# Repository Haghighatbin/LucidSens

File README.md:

# LucidSens

<b>A device for electrochemiluminescence (ECL)-based measurements</b><br /><br />

<p align='justify'>
  There is a common agreement that the most indicative clinical procedure for rapid and early diagnosis of diseases is to monitor the concentration of specific biomarkers in the patient’s analytical sample at the early stages of the incident using point-of-care (POC) technologies. Among the POC sensing devices, luminescence-based sensing methodologies have been a dominant trend in clinical procedures mostly owing to their tremendously high sensitivity, specificity and rapidity in the analysis of multiplex analytical samples. However, achieving high photosensitivity and versatility to process multiple samples in luminescence-based POC devices commonly come at a cost of compromising the affordability aspect of such sensing devices. <br /><br />To address the gap, <b>LucidSens</b>, a cost-effective luminescence-based POC sensing device is developed for highly sensitive and precise determination of electrochemiluminescence (ECL) and chemiluminescence (CL)-based biological samples. While designed to be portable and cost-efficient, the device provides the versatility of operating in two operational modes: <b>incubation</b> and <b>detection</b> modes. In the incubation mode, the integrity of the process is validated and assured by a PID (proportional, integral, derivative) algorithm with a temperature-sensing feedback loop controlling the implemented Peltier heating/cooling module. In the detection mode, the system is capable of collecting ECL/CL signals of up to 18 analytical samples utilizing an implemented silicon-photomultiplier (SiPM) biased by a miniaturized onboard high-voltage power supply and built-in pseudo-potentiostat modules. The portable architecture of the device as well as remarkable photosensitivity, cost-efficiency and convenient operational instruction may propose the current platform as a versatile analytical template to be adapted for a wide range of ECL/CL-based clinical and bio-analytical determinations.</p><br />
  
Designed and developed by <b><aminhb@tutanota.com></b>

# Firmware
The firmware has been written in Micropython (Loboris port ESP32_LoBo_v3.2.24) based on Espressif ESP32-WROVER-B/I modules with 4MB external SPI flash and 8MB PSRAM.<br />
https://github.com/Haghighatbin/LucidSens/tree/master/Firmware

# Software
Created by: PyQt5 and UI code generator 5.15.4 - sourcefile was written in Python 3.5<br />
https://github.com/Haghighatbin/LucidSens/tree/master/Software   <br />
[Screenshot]

# PCB Layout and Schematics
https://github.com/Haghighatbin/LucidSens/tree/master/PCB_Schematics_Layouts

# CAD files
https://github.com/Haghighatbin/LucidSens/tree/master/CADs

# 3D View
https://user-images.githubusercontent.com/10771949/146338794-2b45d992-ebb1-41cf-bab1-338458c2112e.mp4

# Blueprint

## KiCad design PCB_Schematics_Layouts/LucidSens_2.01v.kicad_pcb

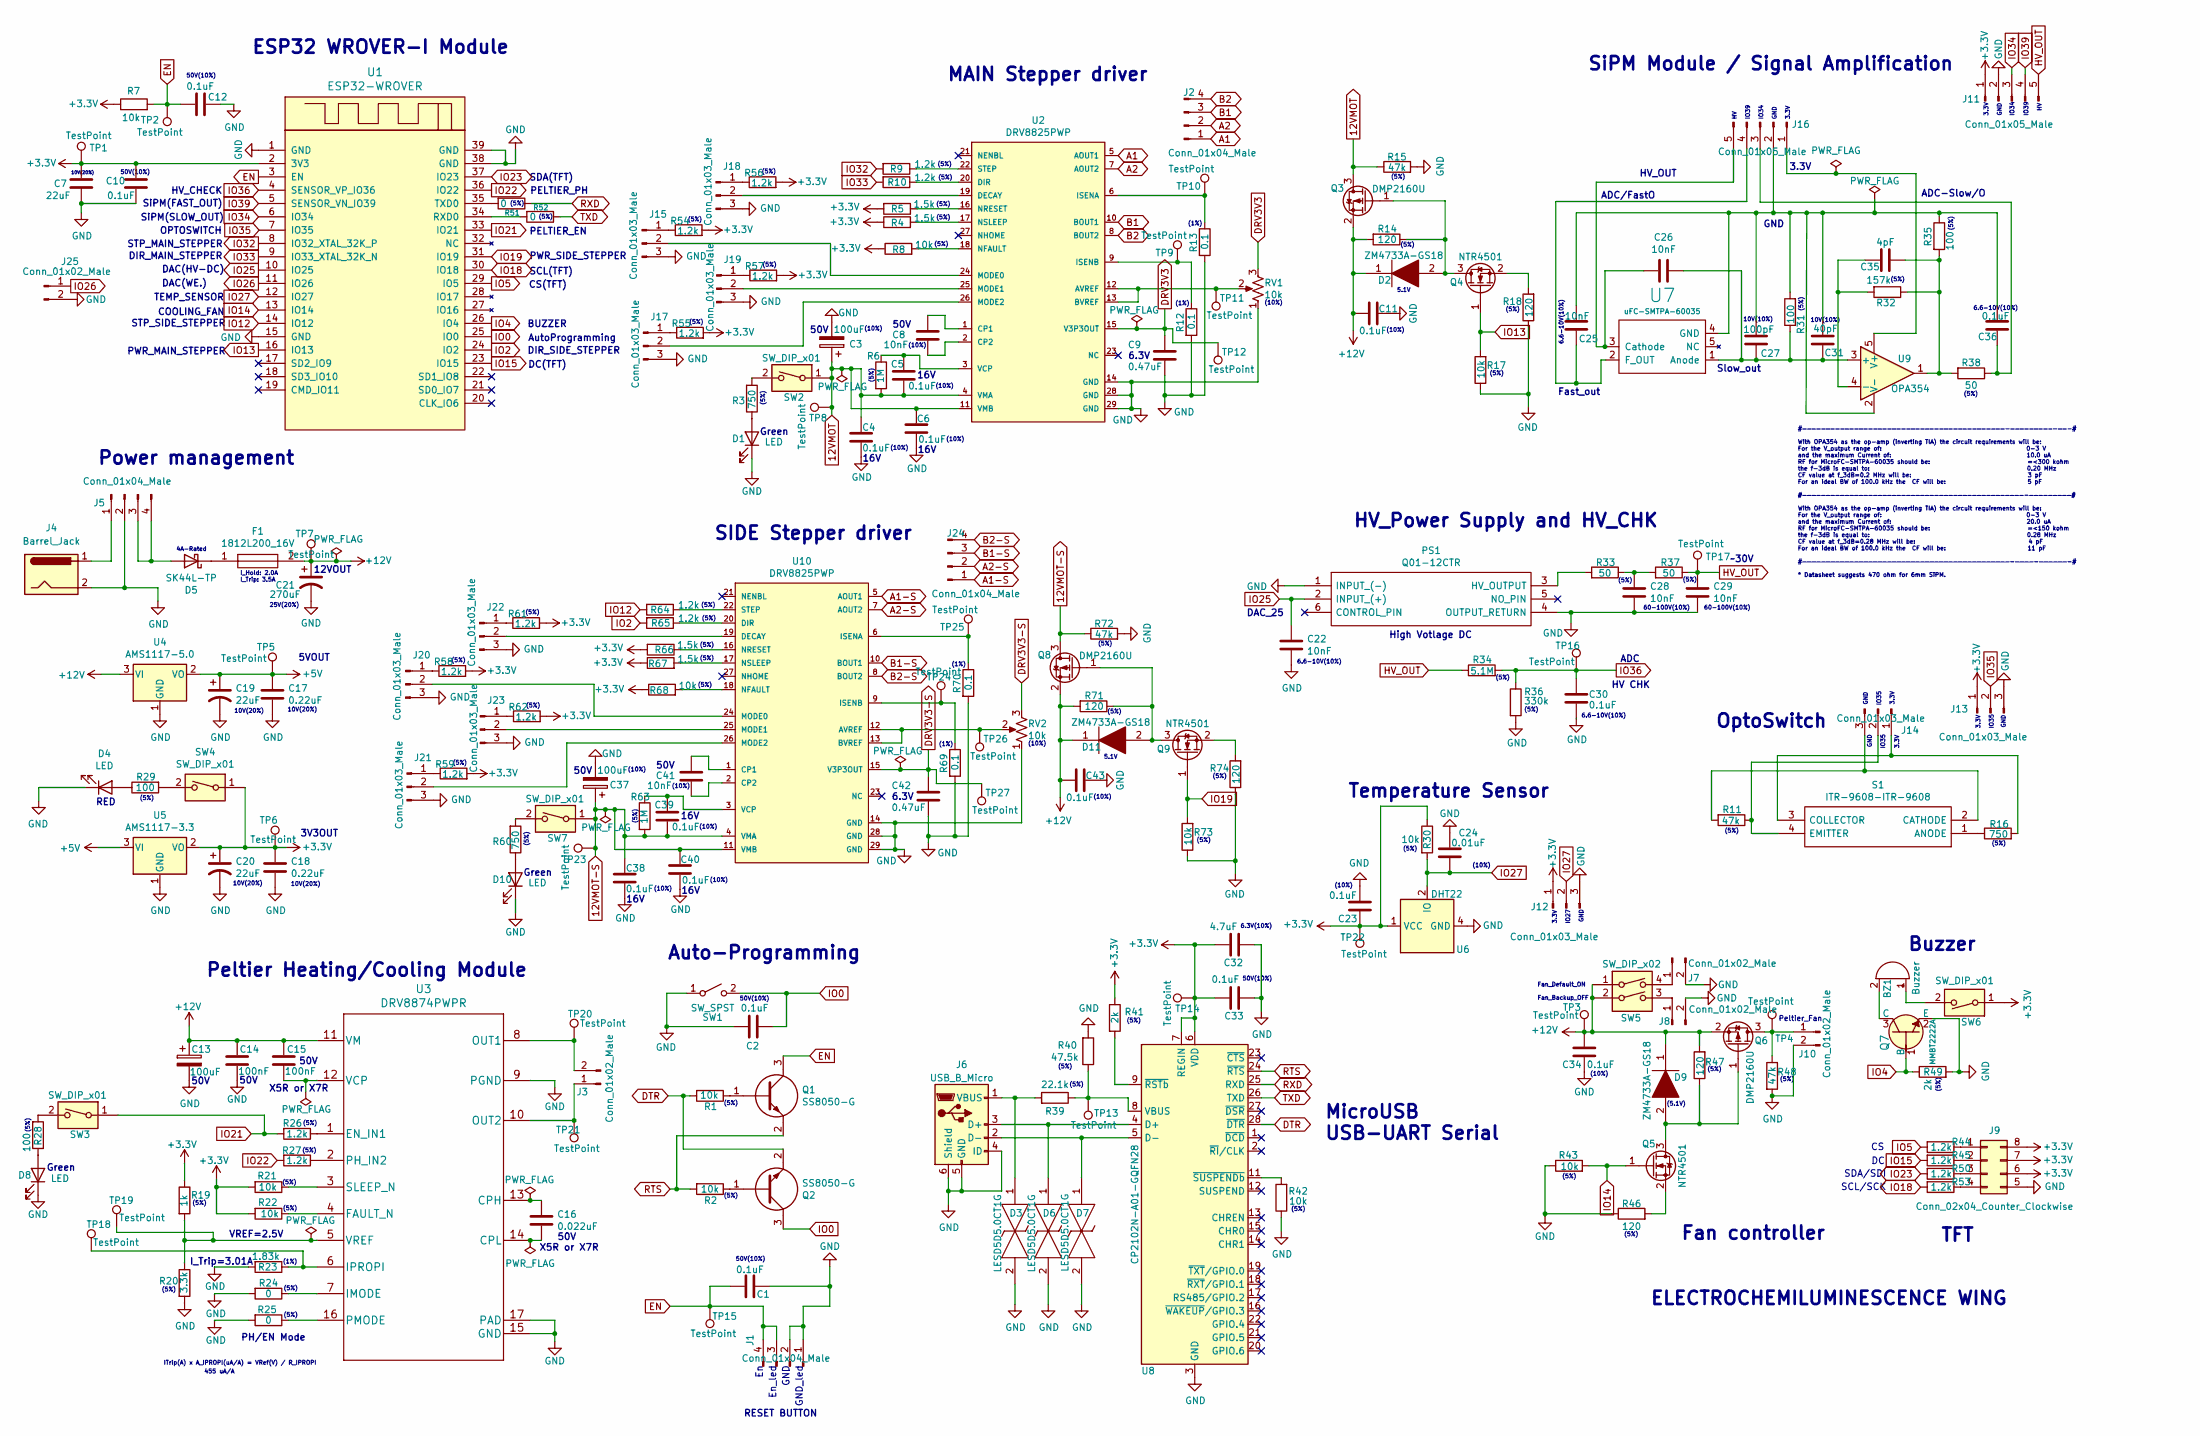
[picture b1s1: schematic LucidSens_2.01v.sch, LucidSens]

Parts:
BZ1: Buzzer; Buzzer_12x9.5RM7.6
C1, C2, C4, C5, C6, C10, C11, C12, C23, C30, C33, C34, C36, C38, C39, C40, C43: 0.1uF; C_0805_2012Metric_Pad1.18x1.45mm_HandSolder
C3, C13, C37: 100uF; CAPAE660X800N
C7: 22uF; C_0805_2012Metric_Pad1.18x1.45mm_HandSolder
C8, C22, C25, C26, C28, C29, C41: 10nF; C_0805_2012Metric_Pad1.18x1.45mm_HandSolder
C9, C42: 0.47uF; C_0805_2012Metric_Pad1.18x1.45mm_HandSolder
C14, C15: 100nF; C_0805_2012Metric_Pad1.18x1.45mm_HandSolder
C16: 0.022uF; C_0805_2012Metric_Pad1.18x1.45mm_HandSolder
C17, C18: 0.22uF; C_0805_2012Metric_Pad1.18x1.45mm_HandSolder
C19, C20: 22uF; CAPAE530X610N
C21: 270uF; CAPAE830X1050N
C24: 0.01uF; C_0805_2012Metric_Pad1.18x1.45mm_HandSolder
C27: 100pF; C_0805_2012Metric_Pad1.18x1.45mm_HandSolder
C31: 40pF; C_0805_2012Metric_Pad1.18x1.45mm_HandSolder
C32: 4.7uF; C_0805_2012Metric_Pad1.18x1.45mm_HandSolder
C35: 4pF; C_0805_2012Metric_Pad1.18x1.45mm_HandSolder
D1, D4, D8, D10: LED; LED_0805_2012Metric
D2, D9, D11: ZM4733A-GS18; MELF_DO-213AB; Manufacturer_Part_Number ZM4733A-GS18; Mouser Part Number 625-ZM4733A-GS18
D3, D6, D7: LESD5D5.0CT1G; LESD5D50CT1G; Manufacturer_Part_Number LESD5D5.0CT1G
D5: SK44L-TP; D_SMC
F1: 1812L200_16V; FUSC4632X180N; Manufacturer_Part_Number 1812L150/24MR; Mouser Part Number 576-1812L150/24MR
J1, J2, J5, J24: Conn_01x04_Male; PhoenixContact_MSTBVA_2,5_4-G-5,08_1x04_P5.08mm_Vertical
J3: Conn_01x02_Male; TerminalBlock_Phoenix_MKDS-1,5-2-5.08_1x02_P5.08mm_Horizont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
J4: Barrel_Jack; BarrelJack_CUI_PJ-063AH_Horizontal
J6: USB_B_Micro; USB_Micro-B_Molex_47346-0001
J7, J8, J10, J25: Conn_01x02_Male; JST_EH_B2B-EH-A_1x02_P2.50mm_Vertical
J9: Conn_02x04_Counter_Clockwise; JST_PHD_B8B-PHDSS_2x04_P2.00mm_Vertical
J11, J16: Conn_01x05_Male; JST_EH_B5B-EH-A_1x05_P2.50mm_Vertical
J12, J13, J14: Conn_01x03_Male; JST_EH_B3B-EH-A_1x03_P2.50mm_Vertical
J15, J17, J18, J19, J20, J21, J22, J23: Conn_01x03_Male; PinHeader_1x03_P2.54mm_Vertical
PS1: Q01-12CTR; Q0112CTR; Manufacturer_Part_Number Q01-12CTR
Q1, Q2: SS8050-G; SOT95P240X115-3N; Manufacturer_Part_Number SS8050-G; Mouser Part Number 750-SS8050-G
Q3, Q6, Q8: DMP2160U; SOT-23
Q4, Q5, Q9: NTR4501; SOT-23
Q7: MMBT2222A; SOT95P240X120-3N; MPN MMBT2222A-7-F; Digi-Key_PN MMBT2222A-FDICT-ND
R1, R2, R7, R8, R17, R21, R22, R30, R42, R43, R68, R73: 10k; R_0805_2012Metric_Pad1.20x1.40mm_HandSolder
R3, R16, R60: 750; R_0805_2012Metric_Pad1.20x1.40mm_HandSolder
R4, R5, R66, R67: 1.5k; R_0805_2012Metric_Pad1.20x1.40mm_HandSolder
R6, R63: 1M; R_0805_2012Metric_Pad1.20x1.40mm_HandSolder
R9, R10, R26, R27, R44, R45, R50, R53, R54, R55, R56, R57, R58, R59, R61, R62, R64, R65: 1.2k; R_0805_2012Metric_Pad1.20x1.40mm_HandSolder
R11, R15, R48, R72: 47k; R_0805_2012Metric_Pad1.20x1.40mm_HandSolder
R12, R13, R69, R70: 0.1; R_0805_2012Metric_Pad1.20x1.40mm_HandSolder
R14, R18, R46, R47, R71, R74: 120; R_0805_2012Metric_Pad1.20x1.40mm_HandSolder
R19: 1k; R_0805_2012Metric_Pad1.20x1.40mm_HandSolder
R20: 3.3k; R_0805_2012Metric_Pad1.20x1.40mm_HandSolder
R23: 1.83k; R_0805_2012Metric_Pad1.20x1.40mm_HandSolder
R24, R25, R51, R52: 0; R_0805_2012Metric_Pad1.20x1.40mm_HandSolder
R28, R29, R31, R35: 100; R_0805_2012Metric_Pad1.20x1.40mm_HandSolder
R32: 157k; R_0805_2012Metric_Pad1.20x1.40mm_HandSolder
R33, R37, R38: 50; R_0805_2012Metric_Pad1.20x1.40mm_HandSolder
R34: 5.1M; R_0805_2012Metric_Pad1.20x1.40mm_HandSolder
R36: 330k; R_0805_2012Metric_Pad1.20x1.40mm_HandSolder
R39: 22.1k; R_0805_2012Metric_Pad1.20x1.40mm_HandSolder
R40: 47.5k; R_0805_2012Metric_Pad1.20x1.40mm_HandSolder
R41, R49: 2k; R_0805_2012Metric_Pad1.20x1.40mm_HandSolder
RV1, RV2: 10k; SM43TW103
S1: ITR-9608-ITR-9608; ITR9608; Manufacturer_Part_Number ITR-9608; Mouser Part Number 638-ITR9608
SW1: SW_SPST; SW_SPST_TL3342
SW2, SW3, SW4, SW6, SW7: SW_DIP_x01; SW_DIP_SPSTx01_Slide_Omron_A6S-110x_W8.9mm_P2.54mm
SW5: SW_DIP_x02; SW_DIP_SPSTx02_Slide_Omron_A6S-210x_W8.9mm_P2.54mm
TP1, TP2, TP3, TP4, TP5, TP6, TP7, TP8, TP9, TP10, TP11, TP12, TP13, TP14, TP15, TP16, TP17, TP18, TP19, TP20, TP21, TP22, TP23, TP24, TP25, TP26, TP27: TestPoint; TestPoint_Pad_D1.5mm
U1: ESP32-WROVER
U2, U10: DRV8825PWP; Texas_Instruments-DRV8825PWP-Level_A; Tolerance 20%; Voltage Rating 100 V
U3: DRV8874PWPR
U4: AMS1117-5.0; SOT-223-3_TabPin2
U5: AMS1117-3.3; SOT-223-3_TabPin2
U6: DHT22; Aosong_DHT11_5.5x12.0_P2.54mm
U7: uFC-SMTPA-60035; uFC-SMTPA-6mm
U8: CP2102N-A01-GQFN28; QFN-28-1EP_5x5mm_P0.5mm_EP3.35x3.35mm
U9: OPA354; SOT-23-5

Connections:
12VMOT: C3.1, C4.1, C5.2, C6.1, Q3.3 (D), R6.2, R15.1, SW2.1, TP8.1, U2.4 (VMA), U2.11 (VMB)
12VMOT-S: C37.1, C38.1, C39.2, C40.1, Q8.3 (D), R63.2, R72.1, SW7.1, TP23.1, U10.4 (VMA), U10.11 (VMB)
+3V3: C7.2, C10.1, C18.1, C20.1, C23.1, C32.1, C33.1, J9.6, J9.7, J9.8, J11.1, J12.1, J13.1, R4.1, R5.2, R7.1, R8.1, R19.1, R21.2, R22.2, R30.1, R41.1, R54.2, R55.2, R56.2, R57.2, R58.2, R59.2, R61.2, R62.2, R66.2, R67.1, R68.1, SW4.1, SW6.1, TP1.1, TP6.1, TP14.1, TP22.1, U1.2 (3V3), U5.2 (VO), U8.6 (VDD), U8.7 (REGIN)
+5V: C17.1, C19.1, TP5.1, U4.2 (VO), U5.3 (VI)
+12V: C11.1, C13.1, C14.1, C15.1, C21.1, C34.1, C43.1, D2.1, D9.1, D11.1, F1.2, Q3.2 (S), Q6.2 (S), Q8.2 (S), R14.2, R47.2, R71.2, SW5.1, SW5.2, TP3.1, TP7.1, U3.11 (VM), U4.3 (VI)
A1: J2.1, U2.5 (AOUT1)
A1-S: J24.1, U10.5 (AOUT1)
A2: J2.2, U2.7 (AOUT2)
A2-S: J24.2, U10.7 (AOUT2)
B1: J2.3, U2.10 (BOUT1)
B1-S: J24.3, U10.10 (BOUT1)
B2: J2.4, U2.8 (BOUT2)
B2-S: J24.4, U10.8 (BOUT2)
DRV3V3: C9.1, RV1.3, TP12.1, U2.15 (V3P3OUT)
DRV3V3-S: C42.1, RV2.3, TP27.1, U10.15 (V3P3OUT)
DTR: Q2.2, R1.2, U8.28 (~DTR)
EN: C1.1, C12.1, J1.3, J1.4, Q1.3, R7.2, TP2.1, TP15.1, U1.3 (EN)
GND: C1.2, C2.1, C3.2, C4.2, C6.2, C7.1, C9.2, C10.2, C11.2, C12.2, C13.2, C14.2, C17.2, C18.2, C19.2, C20.2, C21.2, C22.2, C23.2, C24.2, C28.2, C29.2, C30.2, C32.2, C33.2, C34.2, C37.2, C38.2, C40.2, C42.2, C43.2, D1.1 (K), D3.2, D4.1 (K), D6.2, D7.2, D8.1 (K), D10.1 (K), J1.1, J1.2, J4.2, J5.2, J6.4 (ID), J6.5 (GND), J6.6 (Shield), J7.2, J8.2, J9.5, J10.2, J11.2, J12.3, J13.3, J15.3, J17.3, J18.3, J19.3, J20.3, J21.3, J22.3, J23.3, J25.2, PS1.1 (INPUT_(-)), PS1.4 (OUTPUT_RETURN), Q7.2 (E), R12.2, R13.2, R15.2, R17.1, R18.1, R20.2, R23.2, R24.2, R25.2, R36.2, R40.2, R42.1, R43.1, R46.1, R48.2, R49.2, R69.2, R70.2, R72.2, R73.1, R74.1, RV1.1, RV2.1, SW1.1 (A), U1.1 (GND), U1.15 (GND), U1.38 (GND), U1.39 (GND), U2.14 (GND), U2.28 (GND), U2.29 (GND), U2.~, U3.9 (PGND), U3.15 (GND), U3.17 (PAD), U3.18, U3.19, U3.20, U3.21, U3.22, U3.23, U3.24, U3.25, U3.26, U3.27, U3.28, U3.29, U3.30, U3.31, U3.32, U4.1 (GND), U5.1 (GND), U6.4 (GND), U8.3 (GND), U8.29 (GND), U10.14 (GND), U10.28 (GND), U10.29 (GND), U10.~
HV_OUT: C29.1, J11.5, R34.1, R37.1, TP17.1
IO0: C2.2, Q2.3, SW1.2 (B), U1.25 (IO0)
IO2: R65.2, U1.24 (IO2)
IO4: Q7.1 (B), R49.1, U1.26 (IO4)
IO5: R44.2, U1.29 (IO5)
IO12: R64.2, U1.14 (IO12)
IO13: Q4.1 (G), R17.2, U1.16 (IO13)
IO14: Q5.1 (G), R43.2, U1.13 (IO14)
IO15: R45.2, U1.23 (IO15)
IO18: R53.2, U1.30 (IO18)
IO19: Q9.1 (G), R73.2, U1.31 (IO19)
IO21: R26.2, SW3.1, U1.33 (IO21)
IO22: R27.2, U1.36 (IO22)
IO23: R50.2, U1.37 (IO23)
IO25: C22.1, PS1.2 (INPUT_(+)), U1.10 (IO25)
IO26: J25.1, U1.11 (IO26)
IO27: C24.1, J12.2, R30.2, U1.12 (IO27), U6.2 (IO)
IO32: R9.2, U1.8 (IO32_XTAL_32K_P)
IO33: R10.2, U1.9 (IO33_XTAL_32K_N)
IO34: J11.3, U1.6 (IO34)
IO35: J13.2, U1.7 (IO35)
IO36: C30.1, R34.2, R36.1, TP16.1, U1.4 (SENSOR_VP_IO36)
IO39: J11.4, U1.5 (SENSOR_VN_IO39)
unnamed: BZ1.1 (-), SW6.2
unnamed: BZ1.2 (+), Q7.3 (C)
unnamed: C5.1, R6.1, U2.3 (VCP)
unnamed: C8.1, U2.1 (CP1)
unnamed: C8.2, U2.2 (CP2)
unnamed: C15.2, U3.12 (VCP)
unnamed: C16.1, U3.13 (CPH)
unnamed: C16.2, U3.14 (CPL)
unnamed: C25.1, J16.4, U7.2 (F_OUT)
unnamed: C25.2, C27.2, C31.1, C36.2, J16.2, R31.2, R35.1, U7.4 (GND), U9.2 (V-)
unnamed: C26.1, C27.1, C31.2, R31.1, U7.1 (Anode), U9.3 (+)
unnamed: C26.2, J16.5, U7.3 (Cathode)
unnamed: C28.1, R33.1, R37.2
unnamed: C35.1, R32.2, U9.4 (-)
unnamed: C35.2, R32.1, R35.2, R38.2, U9.1
unnamed: C36.1, J16.3, R38.1
unnamed: C39.1, R63.1, U10.3 (VCP)
unnamed: C41.1, U10.1 (CP1)
unnamed: C41.2, U10.2 (CP2)
unnamed: D1.2 (A), R3.1
unnamed: D2.2, Q3.1 (G), Q4.3 (D), R14.1
unnamed: D3.1, J6.1 (VBUS), R39.2
unnamed: D4.2 (A), R29.1
unnamed: D5.1 (K), F1.1
unnamed: D5.2 (A), J5.3, J5.4
unnamed: D6.1, J6.3 (D+), U8.4 (D+)
unnamed: D7.1, J6.2 (D-), U8.5 (D-)
unnamed: D8.2 (A), R28.1
unnamed: D9.2, Q5.3 (D), Q6.1 (G), R47.1
unnamed: D10.2 (A), R60.1
unnamed: D11.2, Q8.1 (G), Q9.3 (D), R71.1
unnamed: J3.1, TP21.1, U3.10 (OUT2)
unnamed: J3.2, TP20.1, U3.8 (OUT1)
unnamed: J4.1, J5.1
unnamed: J7.1, SW5.4
unnamed: J8.1, SW5.3
unnamed: J9.1, R44.1
unnamed: J9.2, R45.1
unnamed: J9.3, R50.1
unnamed: J9.4, R53.1
unnamed: J10.1, Q6.3 (D), R48.1, TP4.1
unnamed: J14.1, R16.2, S1.3 (COLLECTOR)
unnamed: J14.2, R11.1, S1.4 (EMITTER)
unnamed: J14.3, R11.2, S1.2 (CATHODE)
unnamed: J15.1, R54.1
unnamed: J15.2, U2.24 (MODE0)
unnamed: J16.1, U9.5 (V+)
unnamed: J17.1, R55.1
unnamed: J17.2, U2.26 (MODE2)
unnamed: J18.1, R56.1
unnamed: J18.2, U2.19 (DECAY)
unnamed: J19.1, R57.1
unnamed: J19.2, U2.25 (MODE1)
unnamed: J20.1, R58.1
unnamed: J20.2, U10.24 (MODE0)
unnamed: J21.1, R59.1
unnamed: J21.2, U10.26 (MODE2)
unnamed: J22.1, R61.1
unnamed: J22.2, U10.19 (DECAY)
unnamed: J23.1, R62.1
unnamed: J23.2, U10.25 (MODE1)
unnamed: PS1.3 (HV_OUTPUT), R33.2
unnamed: Q1.1, R1.1
unnamed: Q2.1, R2.1
unnamed: Q4.2 (S), R18.2
unnamed: Q5.2 (S), R46.2
unnamed: Q9.2 (S), R74.2
unnamed: R3.2, SW2.2
unnamed: R4.2, U2.17 (NSLEEP)
unnamed: R5.1, U2.16 (NRESET)
unnamed: R8.2, U2.18 (NFAULT)
unnamed: R9.1, U2.22 (STEP)
unnamed: R10.1, U2.20 (DIR)
unnamed: R12.1, TP9.1, U2.9 (ISENB)
unnamed: R13.1, TP10.1, U2.6 (ISENA)
unnamed: R16.1, S1.1 (ANODE)
unnamed: R19.2, R20.1, TP19.1, U3.5 (VREF)
unnamed: R21.1, U3.3 (SLEEP_N)
unnamed: R22.1, U3.4 (FAULT_N)
unnamed: R23.1, TP18.1, U3.6 (IPROPI)
unnamed: R24.1, U3.7 (IMODE)
unnamed: R25.1, U3.16 (PMODE)
unnamed: R26.1, U3.1 (EN_IN1)
unnamed: R27.1, U3.2 (PH_IN2)
unnamed: R28.2, SW3.2
unnamed: R29.2, SW4.2
unnamed: R39.1, R40.1, TP13.1, U8.8 (VBUS)
unnamed: R41.2, U8.9 (~RSTb)
unnamed: R42.2, U8.11 (~SUSPENDb)
unnamed: R51.2, U1.35 (TXD0)
unnamed: R52.2, U1.34 (RXD0)
unnamed: R60.2, SW7.2
unnamed: R64.1, U10.22 (STEP)
unnamed: R65.1, U10.20 (DIR)
unnamed: R66.1, U10.16 (NRESET)
unnamed: R67.2, U10.17 (NSLEEP)
unnamed: R68.2, U10.18 (NFAULT)
unnamed: R69.1, TP24.1, U10.9 (ISENB)
unnamed: R70.1, TP25.1, U10.6 (ISENA)
unnamed: RV1.2, TP11.1, U2.12 (AVREF), U2.13 (BVREF)
unnamed: RV2.2, TP26.1, U10.12 (AVREF), U10.13 (BVREF)
RTS: Q1.2, R2.2, U8.24 (~RTS)
RXD: R51.1, U8.25 (RXD)
TXD: R52.1, U8.26 (TXD)

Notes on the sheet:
ESP32 WROVER-I Module
DAC(HV-DC)
DIR_MAIN_STEPPER
STP_MAIN_STEPPER
OPTOSWITCH
SiPM(SLOW_OUT)
SiPM(FAST_OUT)
HV_CHECK
PWR_MAIN_STEPPER
BUZZER
DC(TFT)
PELTIER_PH
PELTIER_EN
50V(10%)
(5%)
GND
3.3V
IO34
IO39
IO35
10V(20%)
COOLING_FAN
SCL(TFT)
SDA(TFT)
CS(TFT)
AutoProgramming
TEMP_SENSOR
IO27
#———————————————————————————————————————————-—————————-——-# With OPA354 as the op-amp (inverting TIA) the circuit requirements will be: For the V_output range of: 0-3 V and the maximum Current of: 10.0 uA RF for MicroFC-SMTPA-60035 should be: =<300 kohm the f-3dB is equal to: 0.20 MHz CF value at f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
SiPM Module / Signal Amplification
HV_OUT
6.6-10V(10%)
10V(10%)
ADC/FastO
ADC-Slow/O
Fast_out
Slow_out
(10%)
5.1V
(1%)

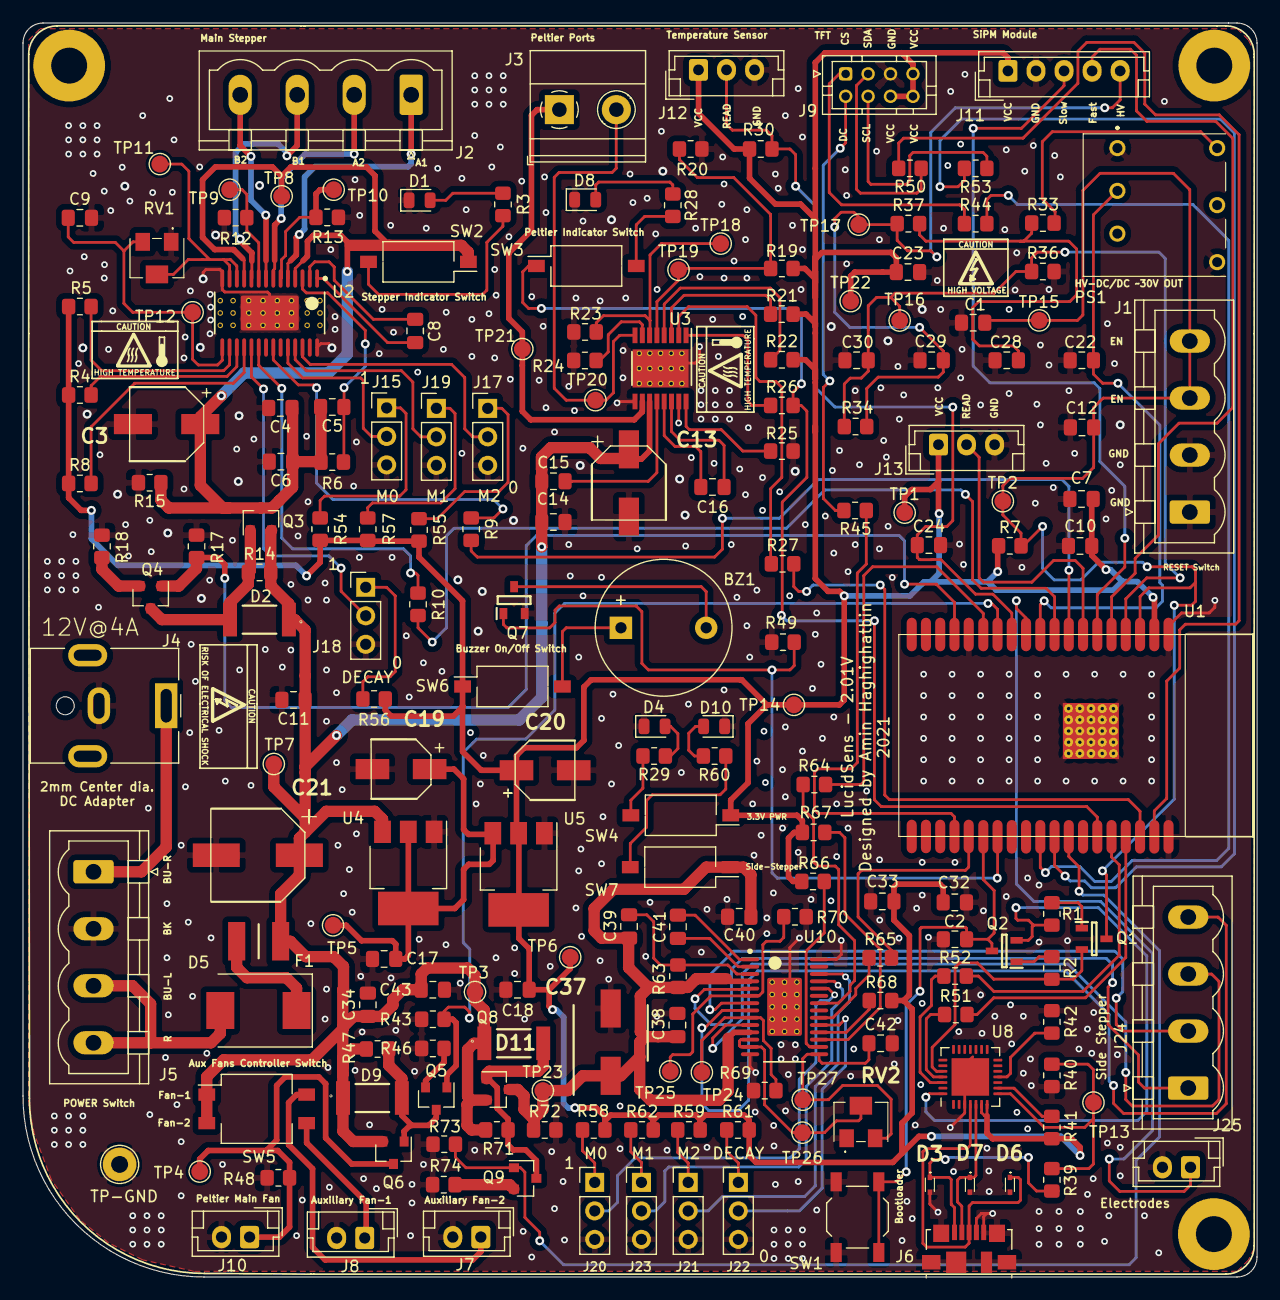
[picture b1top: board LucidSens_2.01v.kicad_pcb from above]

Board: 2 copper layers, 110.0 x 111.8 mm, 194 parts (0 on the bottom side), 133 nets.

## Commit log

2021-12-13 Initial commit after merge
2021-12-16 CAD files and schematics were added
2021-12-20 main _threads modified
2021-12-20 serial connection revised
2025-09-18 Images added.2
2025-09-18 Videos added.
2025-09-18 minor changes in videos.
